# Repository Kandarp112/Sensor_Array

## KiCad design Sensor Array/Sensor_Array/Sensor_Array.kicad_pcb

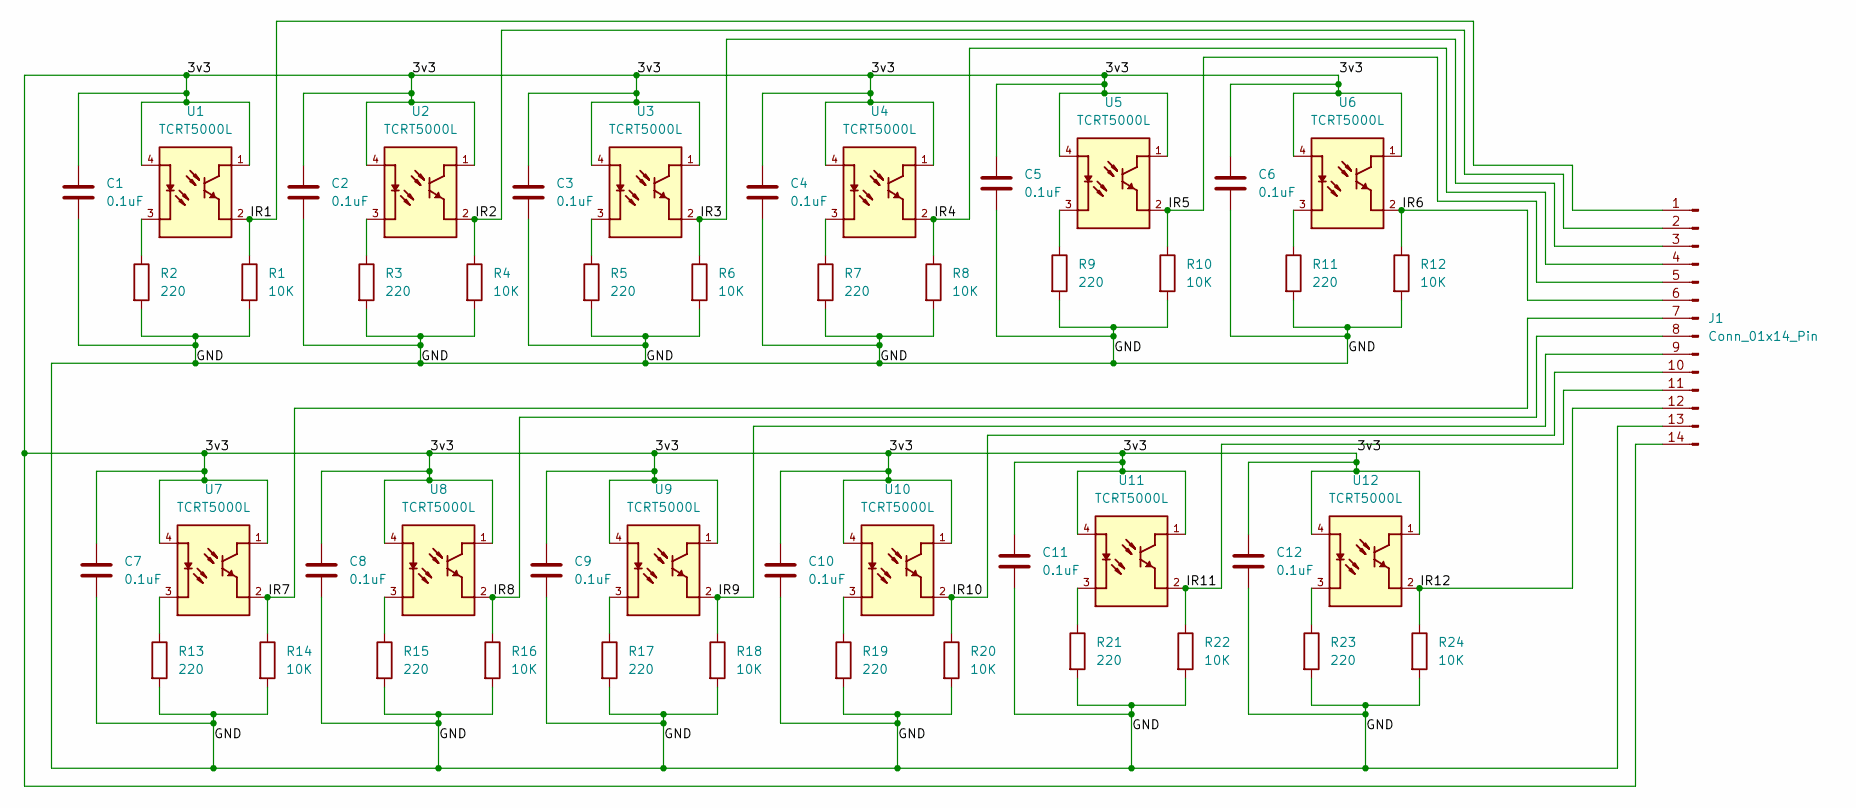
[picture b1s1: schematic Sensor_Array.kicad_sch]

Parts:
C1, C2, C3, C4, C5, C6, C7, C8, C9, C10, C11, C12: 0.1uF; C_0603_1608Metric_Pad1.08x0.95mm_HandSolder
J1: Conn_01x14_Pin; PinHeader_1x14_P2.54mm_Vertical
R1, R4, R6, R8, R10, R12, R14, R16, R18, R20, R22, R24: 10K; R_0603_1608Metric_Pad0.98x0.95mm_HandSolder
R2, R3, R5, R7, R9, R11, R13, R15, R17, R19, R21, R23: 220; R_0603_1608Metric_Pad0.98x0.95mm_HandSolder
U1, U2, U3, U4, U5, U6, U7, U8, U9, U10, U11, U12: TCRT5000L; XDCR_TCRT5000L

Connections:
/3v3: C1.1, C2.1, C3.1, C4.1, C5.1, C6.1, C7.1, C8.1, C9.1, C10.1, C11.1, C12.1, J1.14, U1.1, U1.4, U2.1, U2.4, U3.1, U3.4, U4.1, U4.4, U5.1, U5.4, U6.1, U6.4, U7.1, U7.4, U8.1, U8.4, U9.1, U9.4, U10.1, U10.4, U11.1, U11.4, U12.1, U12.4
/GND: C1.2, C2.2, C3.2, C4.2, C5.2, C6.2, C7.2, C8.2, C9.2, C10.2, C11.2, C12.2, J1.13, R1.2, R2.2, R3.2, R4.2, R5.2, R6.2, R7.2, R8.2, R9.2, R10.2, R11.2, R12.2, R13.2, R14.2, R15.2, R16.2, R17.2, R18.2, R19.2, R20.2, R21.2, R22.2, R23.2, R24.2
/IR1: J1.1, R1.1, U1.2
/IR2: J1.2, R4.1, U2.2
/IR3: J1.3, R6.1, U3.2
/IR4: J1.4, R8.1, U4.2
/IR5: J1.5, R10.1, U5.2
/IR6: J1.6, R12.1, U6.2
/IR7: J1.7, R14.1, U7.2
/IR8: J1.8, R16.1, U8.2
/IR9: J1.9, R18.1, U9.2
/IR10: J1.10, R20.1, U10.2
/IR11: J1.11, R22.1, U11.2
/IR12: J1.12, R24.1, U12.2
unnamed: R2.1, U1.3
unnamed: R3.1, U2.3
unnamed: R5.1, U3.3
unnamed: R7.1, U4.3
unnamed: R9.1, U5.3
unnamed: R11.1, U6.3
unnamed: R13.1, U7.3
unnamed: R15.1, U8.3
unnamed: R17.1, U9.3
unnamed: R19.1, U10.3
unnamed: R21.1, U11.3
unnamed: R23.1, U12.3

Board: 2 copper layers, 49 parts (0 on the bottom side), 26 nets, no tracks yet.

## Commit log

2025-04-29 Add files via upload
    12 sensor array pcb
